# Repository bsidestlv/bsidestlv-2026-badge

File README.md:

# BSidesTLV 2026 Badge

Everything for the BSidesTLV 2026 badge: two KiCad boards, the RP2040 firmware
that runs on it, and the online puzzle challenge — *Alice in AI Land* — that the
badge is used to play.

```
index.html         the challenge - static site, served from the repo root
styles.css  src/  stages/  assets/
hardware/          KiCad projects (CERN-OHL-S-2.0)
  badge/             "JoyFon" - RP2040 handheld, 14 buttons, USB-C
  soldering-kit/     555 + CD4017 LED chaser, the soldering workshop kit
software/          everything that builds the above, but is not served (MIT)
  controller/        RP2040 firmware - enumerates as a DualShock 4
  tools/             slicing and generation, writes into ../assets/
  references/        the source sheets the art was cut from
  legacy/  docs/
```

## The challenge

*Alice in AI Land* is a boulder-pushing puzzle game whose answer is a **program**.
Five stages. The first two are played by hand on the badge. Stage 3 is a
wall: the board is hidden before a human could read it and the move budget
exceeds human input bandwidth, so the only way through is to drive the game with
a script. The game hands you the protocol in stage 2 and dares you to use it.

The simulation is deterministic — 60 ticks/second, one input bitmask per tick,
same seed plus same input trace gives the same outcome byte for byte — which is
what makes it scriptable, replayable and verifiable.

It lives at the repository root — `index.html`, `styles.css`, `src/`, `stages/`
and `assets/` — as plain static files. No server, no build step, every path
relative, so it works at a domain root or under `/<repo>/` unchanged.

```
./serve.sh          # http://localhost:8080, the same files Pages serves
npm run verify      # proves both stages are solvable
```

[`.github/workflows/pages.yml`](.github/workflows/pages.yml) stages those five
paths and publishes them; set Settings -> Pages -> Source to "GitHub Actions"
once and pushes to `main` that touch the site deploy themselves. It stages
rather than uploading the repo so the artifact stays ~4MB instead of ~34MB —
`hardware/` and `software/` are not part of the site.

ES modules need `http://`, not `file://`. That is the only reason a local
server exists.

- [`software/README.md`](software/README.md) — asset set, slicing tools, how every sprite was cut
- [`software/docs/GAME_DESIGN.md`](software/docs/GAME_DESIGN.md) — stages, tick model, protocol

## The hardware

| Board | What | Key parts |
|---|---|---|
| [`hardware/badge/`](hardware/badge) | "JoyFon v0.4" — the badge itself, and the controller the challenge is played on. D-pad, A/B/X/Y, Start/Select, reset and BootSel, all on one side. | RP2040, W25Q128JVS, AMS1117-3.3, USB-C |
| [`hardware/soldering-kit/`](hardware/soldering-kit) | Through-hole LED chaser for the soldering workshop. Beginner-friendly: DIP, axial, CR2032. | TLC555P, CD4017BE, 4x LED, 500k trimmer |

Each project carries its own `production/` directory with the fabrication
package: BOM, positions, designators and IPC netlist.

See [`hardware/README.md`](hardware/README.md) for opening, plotting and
re-fabricating the boards.

## The firmware

[`software/controller/`](software/controller) is the RP2040 firmware. It
presents the badge to a host as a **wired DualShock 4**, which is what makes it
work on an iPhone — iOS only binds controllers it recognizes by USB VID/PID, so
a generic HID gamepad enumerates and is then ignored. Every other host
understands the same report.

```
cd software/controller
mkdir build && cd build
cmake -DPICO_SDK_PATH=/path/to/pico-sdk ..
make -j                              # -> build/controller.uf2
```

Hold `BootSel` while plugging in USB-C, then copy `controller.uf2` onto the
`RPI-RP2` drive that appears. It also builds and runs on a stock Raspberry Pi
Pico, which is the easiest way to try the firmware without a badge.

Full pin map and HID report layout:
[`software/controller/README.md`](software/controller/README.md).

## Licences

- **Software** — MIT, see [`LICENSE`](LICENSE). Covers `software/` and the
  Python/Node tooling under `hardware/soldering-kit/tools/`.
- **Hardware** — CERN-OHL-S-2.0, see [`hardware/LICENSE`](hardware/LICENSE).
  Covers both KiCad projects and every gerber, plot and production package
  under `hardware/`.

Third-party symbols and footprints vendored under
`hardware/badge/libs/lcsc/` keep their own upstream terms.

## Contributing

See [`CONTRIBUTING.md`](CONTRIBUTING.md).

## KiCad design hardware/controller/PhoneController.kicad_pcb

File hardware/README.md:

# Hardware

Two KiCad 9 projects. Each is self-contained: open the `.kicad_pro` in KiCad
and everything it needs is beside it.

| Directory | Project | What it is |
|---|---|---|
| `badge/` | `PhoneController` / "JoyFon v0.4" | The badge, and the controller the online challenge is played on: D-pad, A/B/X/Y, Start/Select, reset and BootSel, USB-C, 16 MB external flash, SWD header. |
| `soldering-kit/` | `BSidesTLV26TinyBadge` | The soldering workshop kit: a TLC555 astable clocking a CD4017 decade counter that chases four LEDs. All through-hole — DIP sockets, axial resistors, a 3296W trimmer for the rate and a CR2032 holder — so a first-time solderer can build it. |

The project files inside `badge/` are still named `PhoneController.*` — that
was the board's working name before it became the badge. The directory says what
it is; renaming the KiCad project would break every path that refers to it.

## Opening

KiCad 9. Nothing here needs a plugin to *view*; the production packages were
generated with [Fabrication Toolkit](https://github.com/bennymeg/Fabrication-Toolkit),
whose settings live in each project's `fabrication-toolkit-options.json`.

`badge/libs/lcsc/` vendors the symbol, footprint and 3D model for the USB-C
connector imported from LCSC. `fp-lib-table` and `sym-lib-table` point at it
with project-relative paths, so the project moves without breaking.

## Fabrication

Each project ships the package it was last ordered with:

```
<project>/production/
  bom.csv           designator -> footprint, quantity, value, LCSC part number
  positions.csv     pick-and-place
  designators.csv
  netlist.ipc       IPC-D-356 netlist, for bare-board electrical test
  <project>.zip     the gerbers as sent to the fab
```

`badge/gerbers/` additionally keeps the loose gerber set and job file, and
`badge/output/` the per-layer SVG plots.

To regenerate rather than reuse: open the board, run Fabrication Toolkit, and
the directory is rewritten.

## Generating the soldering-kit schematic

`soldering-kit/tools/` builds `BSidesTLV26TinyBadge.kicad_sch` from code rather
than by hand:

```
python3 soldering-kit/tools/build_badge_sch.py
```

| File | What |
|---|---|
| `build_badge_sch.py` | The circuit itself: CR2032 -> TLC555 astable -> CD4017 -> 4 LEDs, with the part choices argued in its docstring |
| `schbuild.py` | Places symbols, resolves absolute pin coordinates, draws wires |
| `symlib.py` | Pulls a symbol out of a `.kicad_sym` library, flattening `(extends ...)` so the embedded copy is self-contained |
| `ksexpr.py` | Dependency-free S-expression reader/writer that round-trips KiCad files |
| `verify_xf.py` | Regression check for the pin transform against a pre-change schematic passed as `argv[1]` |

These are software, not hardware: MIT, under the root `LICENSE`.

## Autorouting

`badge/freerouting.dsn` is the Specctra export used with
[Freerouting](https://github.com/freerouting/freerouting). It is an export, not
a source of truth — the `.kicad_pcb` is.

## What is deliberately not here

KiCad's own rolling archives (`*-backups/`, `production/backups/`), the
`fp-info-cache`, `*.kicad_prl` per-user state and editor lock files are all
ignored — git is the history now. See the root `.gitignore`.

## Firmware

The badge's firmware is not here — it is a Pico SDK project at
[`../software/controller/`](../software/controller), under MIT like the rest of
the software.

## Licence

CERN-OHL-S-2.0, see [`LICENSE`](LICENSE). Vendored third-party libraries under
`badge/libs/` keep their upstream terms.

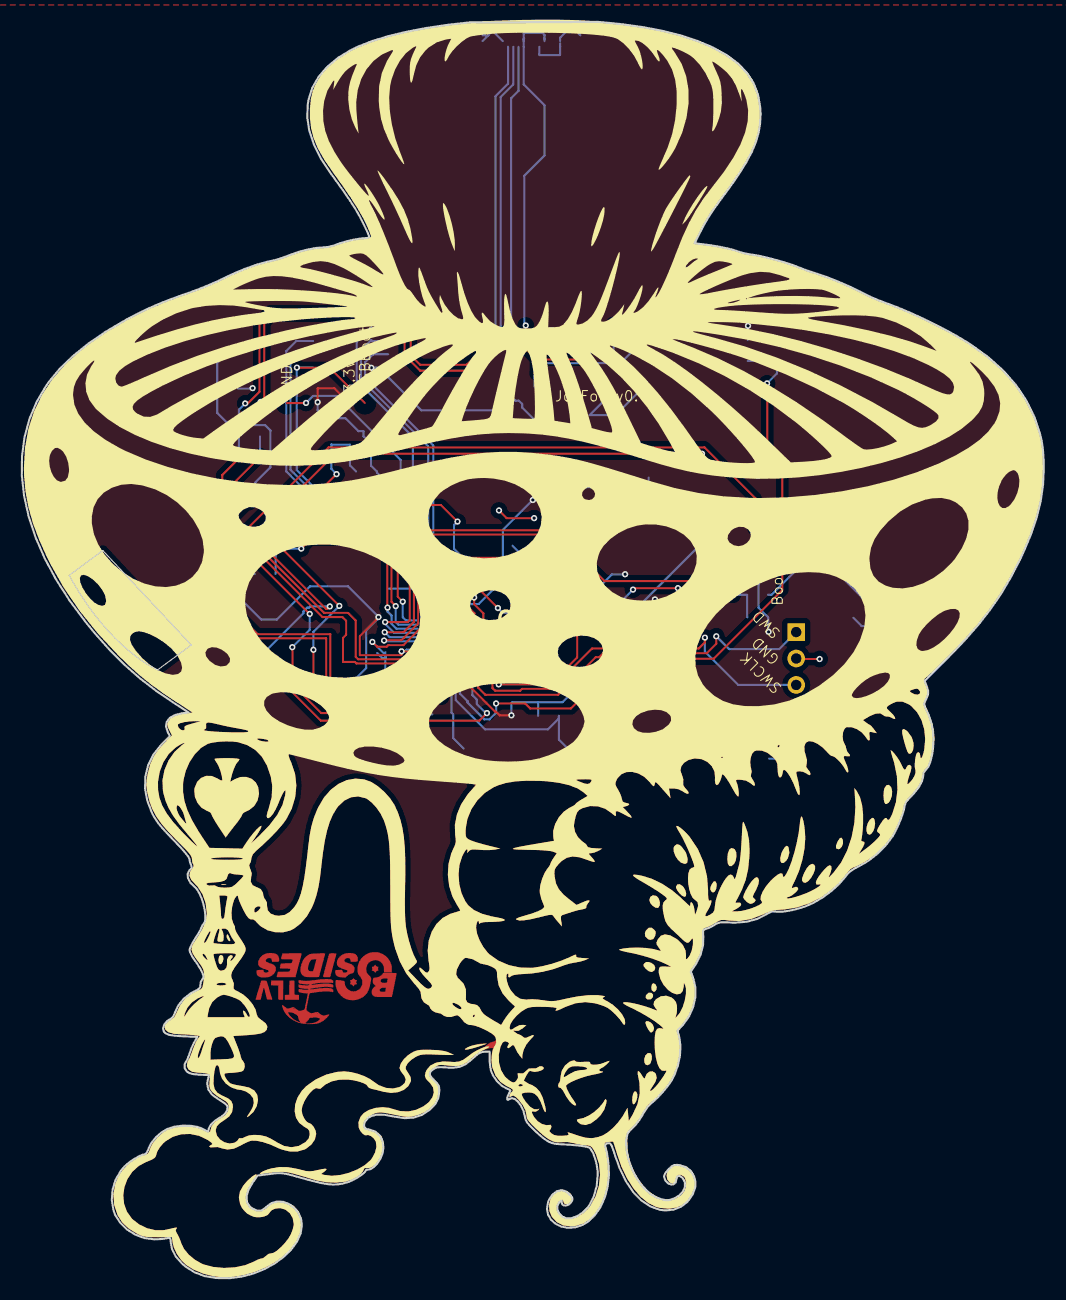
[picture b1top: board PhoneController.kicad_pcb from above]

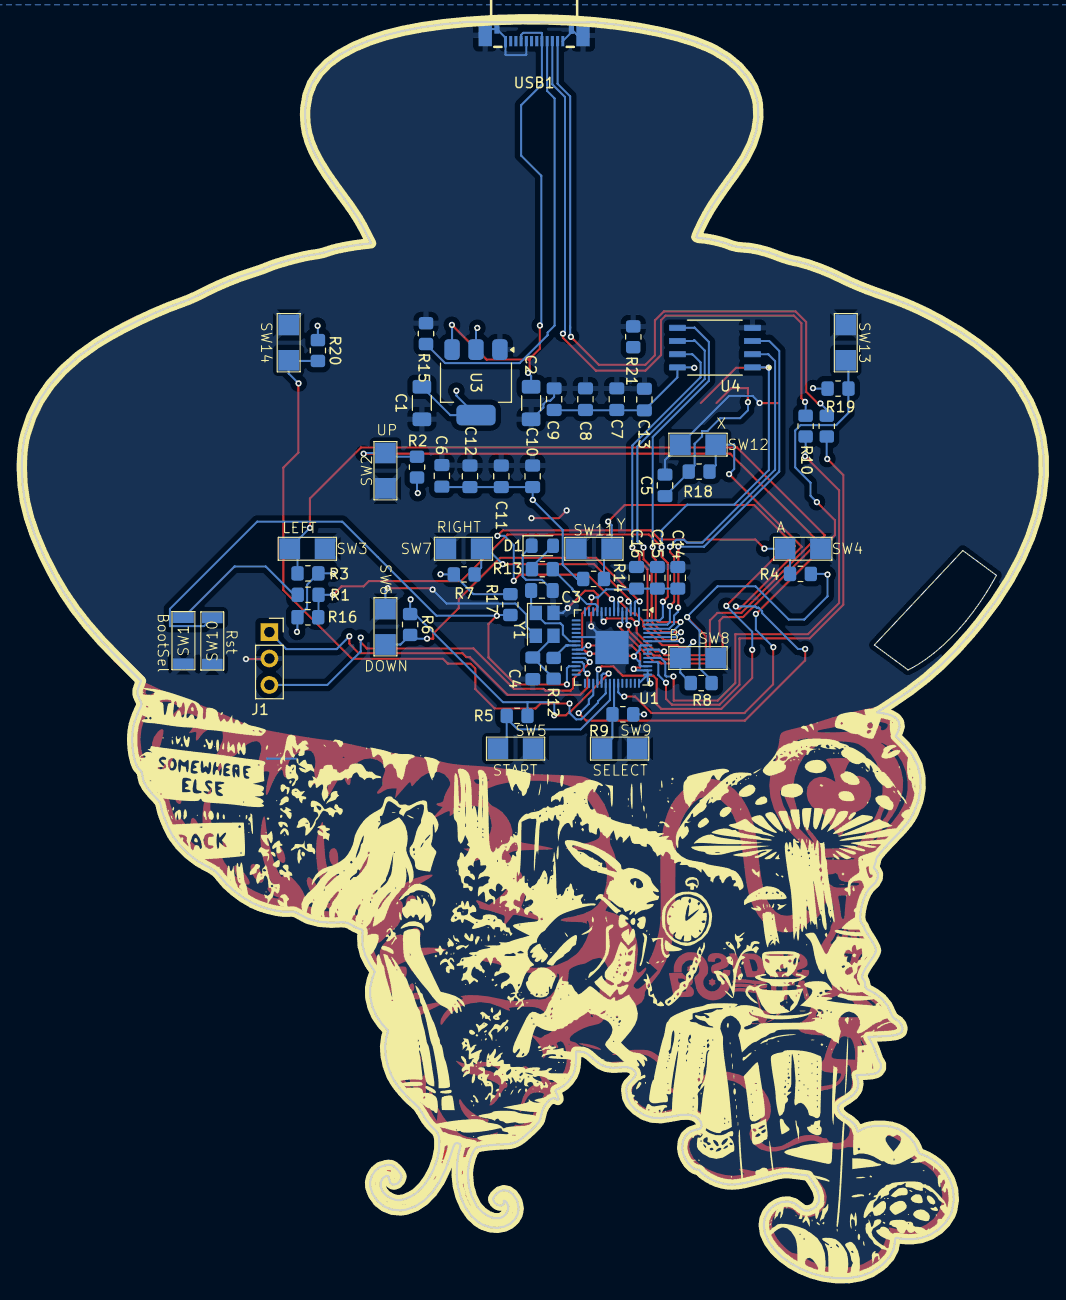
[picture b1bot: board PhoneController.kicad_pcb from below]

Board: 2 copper layers, 98.2 x 120.7 mm, 58 parts (58 on the bottom side), 36 nets.

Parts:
C1, C2: 100uF; C_1206_3216Metric_Pad1.33x1.80mm_HandSolder
C3, C4: 15pF; C_0805_2012Metric_Pad1.18x1.45mm_HandSolder
C5, C6, C7, C8, C9, C10, C11, C12, C14, C15: 100nF; C_0805_2012Metric_Pad1.18x1.45mm_HandSolder
C13, C16: 1uF; C_0805_2012Metric_Pad1.18x1.45mm_HandSolder
D1: LED; LED_0805_2012Metric_Pad1.15x1.40mm_HandSolder
J1: Conn_01x03_Pin; PinSocket_1x03_P2.54mm_Vertical
R1, R2, R3, R4, R5, R6, R7, R8, R9, R12, R14, R18, R19, R20: 1k Ohm; R_0805_2012Metric_Pad1.20x1.40mm_HandSolder
R10, R11: 27.4 Ohm; R_0805_2012Metric_Pad1.20x1.40mm_HandSolder
R13: 300 Ohm; R_0805_2012Metric_Pad1.20x1.40mm_HandSolder
R15, R21: 5.1k Ohm; R_0805_2012Metric_Pad1.20x1.40mm_HandSolder
R16: DNP; R_0805_2012Metric_Pad1.20x1.40mm_HandSolder
R17: 10k Ohm; R_0805_2012Metric_Pad1.20x1.40mm_HandSolder
SW1, SW2, SW3, SW4, SW5, SW6, SW7, SW8, SW9, SW10, SW11, SW12, SW13, SW14: SW_Push; TS-1088-AR02016
U1: RP2040; QFN-56-1EP_7x7mm_P0.4mm_EP3.2x3.2mm
U3: AMS1117-3.3; SOT-223-3_TabPin2
U4: W25Q128JVS; SOIC127P790X216-8N
USB1: TC-002; C3039316_USB-SMD_TC-002_1
Y1: Crystal_GND24; Crystal_SMD_Abracon_ABM8G-4Pin_3.2x2.5mm

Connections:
1.1v: C14.2, C15.2, C16.2, U1.23 (DVDD), U1.45 (VREG_VOUT), U1.50 (DVDD)
3.3v: C1.1, C5.2, C6.2, C7.2, C8.2, C9.2, C10.2, C11.2, C12.2, C13.2, R2.1, R3.1, R4.1, R5.1, R6.1, R7.1, R8.1, R9.1, R14.1, R16.2, R17.2, R18.1, R19.1, R20.1, U1.1 (IOVDD), U1.10 (IOVDD), U1.22 (IOVDD), U1.33 (IOVDD), U1.42 (IOVDD), U1.43 (ADC_AVDD), U1.44 (VREG_IN), U1.48 (USB_VDD), U1.49 (IOVDD), U3.2 (VO), U4.8 (VCC)
BTN_A: R4.2, SW4.2, U1.7 (GPIO5)
BTN_B: R8.2, SW8.2, U1.6 (GPIO4)
BTN_DN: R6.2, SW6.2, U1.2 (GPIO0)
BTN_LT: R3.2, SW3.2, U1.5 (GPIO3)
BTN_RT: R7.2, SW7.2, U1.3 (GPIO1)
BTN_SL: R19.2, SW13.2, U1.37 (GPIO25)
BTN_SLCT: R9.2, SW9.2, U1.36 (GPIO24)
BTN_SR: R20.2, SW14.2, U1.34 (GPIO22)
BTN_STRT: R5.2, SW5.2, U1.35 (GPIO23)
BTN_UP: R2.2, SW2.2, U1.4 (GPIO2)
BTN_X: R18.2, SW12.2, U1.31 (GPIO20)
BTN_Y: R14.2, SW11.2, U1.32 (GPIO21)
CC1: R15.1, USB1.A5 (CC1)
DM: R11.1, USB1.A7 (DN1)
DP: R10.2, USB1.A6 (DP1)
GND: C1.2, C2.2, C3.1, C4.1, C5.1, C6.1, C7.1, C8.1, C9.1, C10.1, C11.1, C12.1, C13.1, C14.1, C15.1, C16.1, D1.1 (K), J1.2, R15.2, R21.2, SW1.1, SW2.1, SW3.1, SW4.1, SW5.1, SW6.1, SW7.1, SW8.1, SW9.1, SW10.1, SW11.1, SW12.1, SW13.1, SW14.1, U1.19 (TESTEN), U1.57 (GND), U3.1 (GND), U4.4 (GND), USB1.0 (GND), USB1.1 (GND), USB1.A1 (GND), USB1.A12 (GND), USB1.B12 (GND), Y1.2, Y1.4
unnamed: C4.2, R12.1, Y1.3
unnamed: D1.2 (A), R13.2
unnamed: R13.1, U1.11 (GPIO8)
unnamed: R11.2, U1.46 (USB_DM)
unnamed: R10.1, U1.47 (USB_DP)
unnamed: C3.2, U1.20 (XIN), Y1.1
unnamed: R12.2, U1.21 (XOUT)
QSPI_SCLK: U1.52 (QSPI_SCLK), U4.6 (CLK)
QSPI_SD0: U1.53 (QSPI_SD0), U4.5 (DI(IO0))
QSPI_SD1: U1.55 (QSPI_SD1), U4.2 (DO(IO1))
QSPI_SD2: U1.54 (QSPI_SD2), U4.3 (IO2)
QSPI_SD3: U1.51 (QSPI_SD3), U4.7 (IO3)
QSPI_SS: R1.1, R16.1, U1.56 (QSPI_SS), U4.1 (~CS)
RUN: R17.1, SW10.2, U1.26 (RUN)
SWCLK: J1.3, U1.24 (SWCLK)
SWD: J1.1, U1.25 (SWD)
VCC: C2.1, U3.3 (VI), USB1.A4 (VBUS), USB1.B9 (VBUS)
~USB_BOOT: R1.2, SW1.2

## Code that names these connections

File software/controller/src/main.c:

/*
 * JoyFon controller - a USB HID game controller for the Raspberry Pi Pico.
 *
 * Mimics a Game Boy Color button layout (D-pad + A/B + START/SELECT) and
 * presents itself to a host as a wired DualShock 4.
 *
 * A generic HID gamepad works on Android, PC and Linux but is invisible on
 * iOS/iPadOS: Apple's GameController framework only attaches to controllers
 * it recognises by USB VID/PID. Speaking the DualShock 4's identity and
 * input report gets an iPhone to bind a real controller profile, and the
 * same descriptor is understood everywhere else too.
 *
 * Wiring (all buttons are active-low, i.e. wired to GND, using the internal
 * pull-ups - external pull-ups are also fine):
 *
 *   GPIO0  -> D-pad DOWN
 *   GPIO1  -> D-pad RIGHT
 *   GPIO2  -> D-pad UP
 *   GPIO3  -> D-pad LEFT
 *   GPIO4  -> B
 *   GPIO5  -> A
 *   GPIO20 -> X
 *   GPIO21 -> Y
 *   GPIO22 -> SR (right shoulder)
 *   GPIO25 -> SL (left shoulder)
 *   GPIO23 -> START
 *   GPIO24 -> SELECT
 *   GPIO8  -> status LED (active-high)
 */

#include <string.h>

#include "pico/stdlib.h"
#include "tusb.h"

#include "usb_descriptors.h"
#include "ds4.h"

//--------------------------------------------------------------------+
// Pin configuration
//--------------------------------------------------------------------+

#define PIN_DOWN    0u
#define PIN_RIGHT   1u
#define PIN_UP      2u
#define PIN_LEFT    3u
#define PIN_B       4u
#define PIN_A       5u
#define PIN_X       20u
#define PIN_Y       21u
#define PIN_SR      22u
#define PIN_SL      25u
#define PIN_START   23u
#define PIN_SELECT  24u

#define PIN_LED     8u

// All face/dpad buttons used by the controller, so we can init them in a loop.
static const uint8_t k_button_pins[] = {
  PIN_DOWN, PIN_RIGHT, PIN_UP, PIN_LEFT,
  PIN_B, PIN_A, PIN_X, PIN_Y, PIN_SR, PIN_SL, PIN_START, PIN_SELECT,
};

// Buttons are active-low (pressed == logic 0 thanks to the pull-up).
static inline bool button_pressed(uint8_t pin)
{
  return !gpio_get(pin);
}

//--------------------------------------------------------------------+
// Status LED
//--------------------------------------------------------------------+

// Blink intervals (ms) signalling the USB connection state.
enum {
  BLINK_NOT_MOUNTED = 250,
  BLINK_SUSPENDED   = 1000,
};

// 0 means "don't blink, let the application drive the LED directly".
static uint32_t blink_interval_ms = BLINK_NOT_MOUNTED;

static inline uint32_t now_ms(void)
{
  return to_ms_since_boot(get_absolute_time());
}

static void board_setup(void)
{
  for ( size_t i = 0; i < sizeof(k_button_pins) / sizeof(k_button_pins[0]); i++ )
  {
    uint8_t pin = k_button_pins[i];
    gpio_init(pin);
    gpio_set_dir(pin, GPIO_IN);
    // gpio_pull_up(pin);
  }

  gpio_init(PIN_LED);
  gpio_set_dir(PIN_LED, GPIO_OUT);
  gpio_put(PIN_LED, 0);
}

//--------------------------------------------------------------------+
// USB device callbacks
//--------------------------------------------------------------------+

void tud_mount_cb(void)
{
  blink_interval_ms = 0; // application now controls the LED
}

void tud_umount_cb(void)
{
  blink_interval_ms = BLINK_NOT_MOUNTED;
}

void tud_suspend_cb(bool remote_wakeup_en)
{
  (void) remote_wakeup_en;
  blink_interval_ms = BLINK_SUSPENDED;
}

void tud_resume_cb(void)
{
  blink_interval_ms = tud_mounted() ? 0 : BLINK_NOT_MOUNTED;
}

//--------------------------------------------------------------------+
// DualShock 4 input report
//--------------------------------------------------------------------+

static uint8_t compute_hat(bool up, bool down, bool left, bool right)
{
  // Opposite directions cancel out so we never report an impossible diagonal.
  if (up && down)    { up = down = false; }
  if (left && right) { left = right = false; }

  if (up && right)   return DS4_HAT_NE;
  if (up && left)    return DS4_HAT_NW;
  if (down && right) return DS4_HAT_SE;
  if (down && left)  return DS4_HAT_SW;
  if (up)            return DS4_HAT_N;
  if (down)          return DS4_HAT_S;
  if (left)          return DS4_HAT_W;
  if (right)         return DS4_HAT_E;
  return DS4_HAT_NONE;
}

static void build_report(ds4_input_report_t *report, uint8_t counter, uint16_t timestamp)
{
  memset(report, 0, sizeof(*report));

  // No analog sticks on this board: report both centred and both triggers released.
  report->lx = report->ly = DS4_STICK_CENTER;
  report->rx = report->ry = DS4_STICK_CENTER;

  report->buttons0 = compute_hat(
      button_pressed(PIN_UP),
      button_pressed(PIN_DOWN),
      button_pressed(PIN_LEFT),
      button_pressed(PIN_RIGHT));

  // Game Boy face buttons map onto the DualShock diamond in the same positions.
  if (button_pressed(PIN_A))      report->buttons0 |= DS4_BTN_CROSS;
  if (button_pressed(PIN_B))      report->buttons0 |= DS4_BTN_CIRCLE;
  if (button_pressed(PIN_X))      report->buttons0 |= DS4_BTN_SQUARE;
  if (button_pressed(PIN_Y))      report->buttons0 |= DS4_BTN_TRIANGLE;

  if (button_pressed(PIN_SL))     report->buttons1 |= DS4_BTN_L1;
  if (button_pressed(PIN_SR))     report->buttons1 |= DS4_BTN_R1;
  if (button_pressed(PIN_START))  report->buttons1 |= DS4_BTN_OPTIONS;
  if (button_pressed(PIN_SELECT)) report->buttons1 |= DS4_BTN_SHARE;

  // The low two bits of buttons2 are PS and touchpad-click; the counter lives
  // in the upper six and must advance on every report.
  report->buttons2 = (uint8_t) (counter << 2);

  report->timestamp   = timestamp;
  report->status      = DS4_STATUS_FULL;
  report->touch_count = 0;
}

// Poll buttons and stream a report to the host. Unlike a generic HID gamepad
// we send on every interval rather than only on change: the real controller
// streams continuously, and the report counter has to keep moving for drivers
// that use it to detect a stalled device.
static void hid_task(void)
{
  const uint32_t poll_interval_ms = 5;
  static uint32_t last_poll_ms = 0;
  static uint8_t counter = 0;
  static uint16_t timestamp = 0;

  if ( now_ms() - last_poll_ms < poll_interval_ms ) return;
  last_poll_ms = now_ms();

  ds4_input_report_t report;
  build_report(&report, counter, timestamp);

  // Wake the host if we are suspended and the user presses something.
  if ( tud_suspended() )
  {
    if ( (report.buttons0 & 0xF0) || report.buttons1 ||
         (report.buttons0 & 0x0F) != DS4_HAT_NONE )
    {
      tud_remote_wakeup();
    }
    return;
  }

  if ( !tud_hid_ready() ) return;

  if ( tud_hid_report(DS4_REPORT_ID_INPUT, &report, sizeof(report)) )
  {
    counter = (uint8_t) ((counter + 1) & 0x3F);
    // 5.33 us ticks, so a 5 ms interval advances the stamp by ~938.
    timestamp = (uint16_t) (timestamp + 938);
  }
}

//--------------------------------------------------------------------+
// LED feedback
//--------------------------------------------------------------------+

static void led_task(void)
{
  // When mounted (blink_interval_ms == 0) light the LED while any input is
  // active, giving immediate tactile feedback. Otherwise blink to signal the
  // current USB state.
  if ( blink_interval_ms == 0 )
  {
    bool any = false;

    for ( size_t i = 0; i < sizeof(k_button_pins) / sizeof(k_button_pins[0]); i++ )
    {
      if ( button_pressed(k_button_pins[i]) ) { /* any = true; */  break; }
    }

    gpio_put(PIN_LED, any);
    return;
  }

  static uint32_t last_toggle_ms = 0;
  static bool led_on = false;

  if ( now_ms() - last_toggle_ms < blink_interval_ms ) return;
  last_toggle_ms = now_ms();

  led_on = !led_on;
  gpio_put(PIN_LED, led_on);
}

//--------------------------------------------------------------------+
// Main
//--------------------------------------------------------------------+

int main(void)
{
  board_setup();

  tud_init(BOARD_TUD_RHPORT);

  while (1)
  {
    tud_task();   // service the USB device stack
    hid_task();   // read buttons and send reports
    led_task();   // status / activity LED
  }
}
